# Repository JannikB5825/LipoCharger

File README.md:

# LipoCharger
Single Cell Lipo charger with battery protection and 5V DC-DC converter.

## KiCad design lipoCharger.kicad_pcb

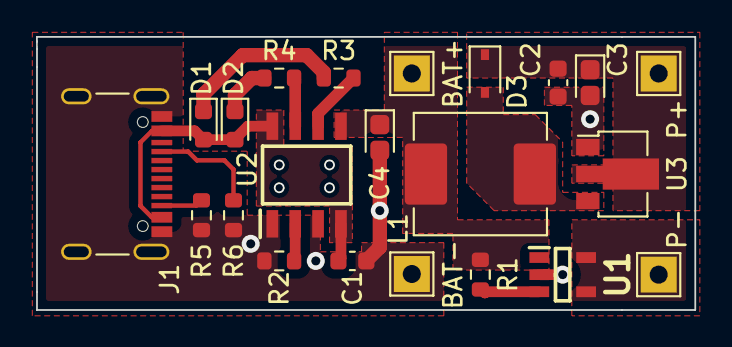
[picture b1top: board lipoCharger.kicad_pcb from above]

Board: 2 copper layers, 36.6 x 15.2 mm, 22 parts (0 on the bottom side), 14 nets.

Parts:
BAT+: TestPoint_THTPad_2.0x2.0mm_Drill1.0mm
BAT-: TestPoint_THTPad_2.0x2.0mm_Drill1.0mm
C1: 10uF; C_0603_1608Metric
C2: 100nF; C_0603_1608Metric
C3, C4: 100uF; CP_EIA-1608-08_AVX-J
D1, D2: LED; LED_0603_1608Metric
D3: 1N5817; D_SOD-323
J1: USB_C_Receptacle_Palconn_UTC16-G
L1: 22uH; L_Abracon_ASPI-0630LR
P+: TestPoint_THTPad_2.0x2.0mm_Drill1.0mm
P-: TestPoint_THTPad_2.0x2.0mm_Drill1.0mm
R1: 100; R_0603_1608Metric
R2: 2.2k; R_0603_1608Metric
R3, R4: 510; R_0603_1608Metric
R5, R6: 5.1k; R_0603_1608Metric
U1: DW02C; SOT95P290X124-5N
U2: ME4057ASPG-NA; SOIC127P600X180-8N
U3: ME2110A50PG; SOT-89-3

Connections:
+BATT: BAT+.1, C4.1, L1.2, R1.2, U2.5 (BAT)
/CHRG: R4.2, U2.7 (CHRG)
/LX: D3.2 (A), L1.1, U3.3 (LX)
/PROG: R2.2, U2.2 (PROG)
/STBY: R3.2, U2.6 (STDBY)
GND: BAT-.1, C1.2, C2.2, C3.2, C4.2, J1.A1 (GND), J1.A12 (GND), J1.B1 (GND), J1.B12 (GND), J1.S1 (SHIELD), R2.1, R5.2, R6.1, U1.2 (GND), U2.1 (TEMP), U2.3 (GND), U3.1 (GND)
unnamed: D1.1 (K), R3.1
unnamed: D2.1 (K), R4.1
unnamed: J1.A5 (CC1), R6.2
unnamed: J1.B5 (CC2), R5.1
unnamed: R1.1, U1.3 (VDD)
P+: C2.1, C3.1, D3.1 (K), P+.1, U3.2 (VOUT)
P-: P-.1, U1.4 (VM_1), U1.5 (VM_2)
VBUS: C1.1, D1.2 (A), D2.2 (A), J1.A4 (VBUS), J1.A9 (VBUS), J1.B4 (VBUS), J1.B9 (VBUS), U2.4 (VCC), U2.8 (CE)

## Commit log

2022-11-25 post
